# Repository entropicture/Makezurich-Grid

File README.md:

# Makezurich-Grid
Makezurich Grid Challenge

**Caution:** The board has to be powered by an external power supply while programming by FTDI. The power supply has to be good enough to provide the necessary current to the device, both when uploading the code and during regular operation.

How to setup your development environment for uBlox NINA-W102
------------------------------------------
https://github.com/rac2030/IoT-conference-badge/wiki/How-to-setup-your-development-environment

Board (ESP32 based): http://rac.su/project/nina-w102-minimal-breakout/

Kicad software
--------------
http://kicad-pcb.org/

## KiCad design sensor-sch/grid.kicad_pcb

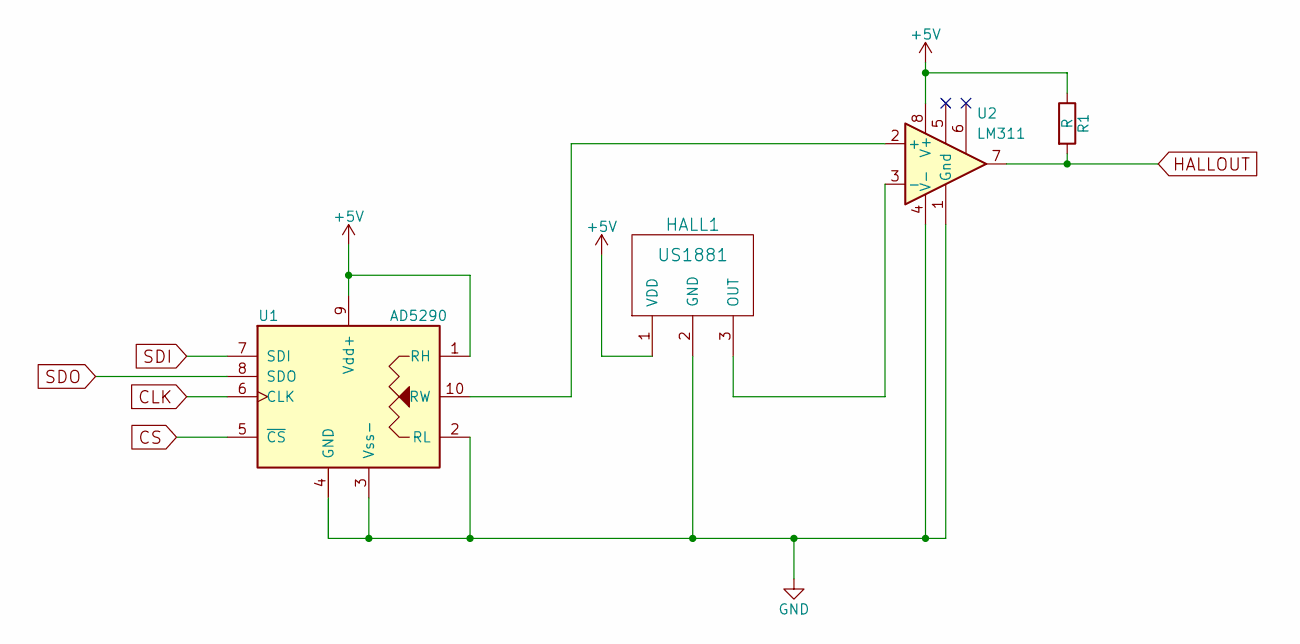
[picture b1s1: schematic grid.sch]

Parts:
HALL1: US1881; HTFS-Series_LEM-HallEffektCurrentTransducer
R1: R; R_0201
U1: AD5290; MSOP-10_3x3mm_Pitch0.5mm
U2: LM311; VSSOP-8_2.3x2mm_Pitch0.5mm

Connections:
+5V: HALL1.1 (VDD), R1.1, U1.1 (RH), U1.9 (Vdd+), U2.8 (V+)
CLK: U1.6 (CLK)
CS: U1.5 (~CS~)
GND: HALL1.2 (GND), U1.2 (RL), U1.3 (Vss-), U1.4 (GND), U2.1 (Gnd), U2.4 (V-)
HALLOUT: R1.2, U2.7
unnamed: HALL1.3 (OUT), U2.3 (-)
unnamed: U1.10 (RW), U2.2 (+)
SDI: U1.7 (SDI)
SDO: U1.8 (SDO)

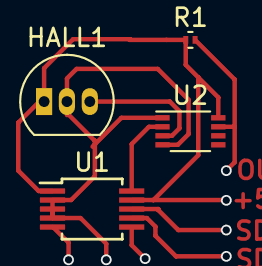
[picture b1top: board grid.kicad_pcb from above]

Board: 2 copper layers, 4 parts (0 on the bottom side), 5 nets.

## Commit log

2018-07-02 Schematic
2018-07-02 ESP32 MQTT blink for the monkey
2018-07-02 Readme update
